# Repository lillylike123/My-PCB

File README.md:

# My-PCB
My first ever PCB, which didn't go so well, but it taught me how to use KiCad and the main editors in the software. It is a PCB that has an LED!!!

I put the Gerber files for the Git repo. Next time, I'll look into the different parts and spend more time. For now, I am very proud of myself.

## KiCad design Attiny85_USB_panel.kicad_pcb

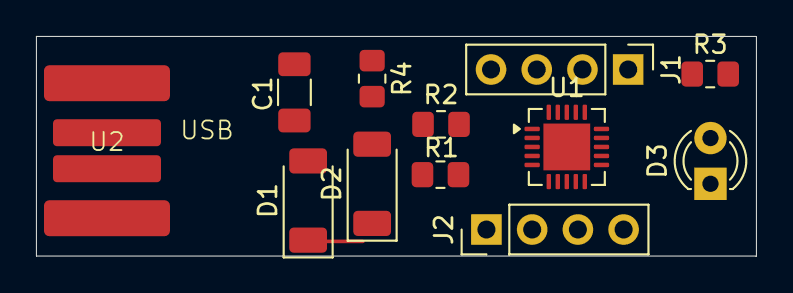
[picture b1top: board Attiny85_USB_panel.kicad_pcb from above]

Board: 2 copper layers, 40.0 x 12.2 mm, 12 parts (0 on the bottom side), 11 nets.

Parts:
C1: 100n; C_1206_3216Metric_Pad1.33x1.80mm_HandSolder
D1, D2: 3V6; D_SOD-128
D3: LED; LED_D3.0mm
J1: SO8-1-4; PinHeader_1x04_P2.54mm_Vertical
J2: SO8-5-8; PinHeader_1x04_P2.54mm_Vertical
R1, R2: 68R; R_0805_2012Metric_Pad1.20x1.40mm_HandSolder
R3: 330R; R_0805_2012Metric_Pad1.20x1.40mm_HandSolder
R4: 1k5; R_0805_2012Metric_Pad1.20x1.40mm_HandSolder
U1: ATtiny85-20M; QFN-20-1EP_4x4mm_P0.5mm_EP2.6x2.6mm
U2: PCB_USB_connector

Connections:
+5V: C1.1, J2.4 (Pin_1), R4.1, U1.8 (VCC), U2.1 (Vcc)
GND: C1.2, D1.2 (A), D2.2 (A), D3.1 (K), J1.4 (Pin_1), U1.4 (GND), U1.21 (GND), U2.4 (GND)
unnamed: D1.1 (K), R2.2, R4.2, U2.2 (D+)
unnamed: D2.1 (K), R1.2, U2.3 (D-)
unnamed: D3.2 (A), R3.1
unnamed: J1.3 (Pin_2), R1.1, U1.3 (XTAL2/PB4)
unnamed: J1.2 (Pin_3), R2.1, U1.2 (XTAL1/PB3)
unnamed: J1.1 (Pin_4), U1.1 (~RESET/PB5)
unnamed: J2.3 (Pin_2), U1.7 (PB2)
unnamed: J2.2 (Pin_3), R3.2, U1.6 (PB1)
unnamed: J2.1 (Pin_4), U1.5 (AREF/PB0)

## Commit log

2026-06-14 Update README with project reflections and next steps
    Added personal reflections and future plans regarding PCB project.
